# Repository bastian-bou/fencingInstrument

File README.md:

[![CC BY-NC-SA 4.0][cc-by-nc-sa-shield]][cc-by-nc-sa]

This work is licensed under a
[Creative Commons Attribution-NonCommercial-ShareAlike 4.0 International License][cc-by-nc-sa].

[![CC BY-NC-SA 4.0][cc-by-nc-sa-image]][cc-by-nc-sa]

[cc-by-nc-sa]: http://creativecommons.org/licenses/by-nc-sa/4.0/
[cc-by-nc-sa-image]: https://licensebuttons.net/l/by-nc-sa/4.0/88x31.png
[cc-by-nc-sa-shield]: https://img.shields.io/badge/License-CC%20BY--NC--SA%204.0-lightgrey.svg

# Antiphona

This is an art project name Antiphona from the artist [Alexandra Riss](https://alexandra-riss.fr/).

It transforms the movements of a fencer during a fight into musical notes.
The fight becomes a unique music.

The device consists of two tripods on either side of the fencing piste.
Each tripod consists of 3 IR sensors spaced 50cm apart and an electronic interface PCB between an arduino micro and the 3 sensors.

## Hardware

IR Sensors are tfmini-s [datasheet](pj2-sj-pm-tfmini-s-a00-product-mannual-en-2155.pdf)

They need 5V DC power supply but the communication is through a LVTTL (3.3V) UART interface.

As the result, the PCB include a level shifter from 3.3V to 5V for the arduino and because the arduino will interrogate each sensor one after the other, there is a 3-way analog multiplexer for each communication channel (RX, TX).  
The PCB also include decoupling capacitors, as all components including sensors are powered by the 5V from the USB port on the arduino.

## Software

To communicate with sensors, I made my own library according to the datasheet with only the functionalities I needed and my specificities, which were:
- multipexer management,
- retrieval of values from the 3 lidars,
- selection of the right value on the 3 sensors

Every 20ms we interrogate the sensors, and play a MIDI note on the USB interface only if a new valid distance is received.  
The MIDI note is played as a function of distance and relative speed. Each meter on the track corresponds to a note from C3 to B4, and the speed (as a function of the distance separating the old value from the new one) corresponds to the velocity of the note.

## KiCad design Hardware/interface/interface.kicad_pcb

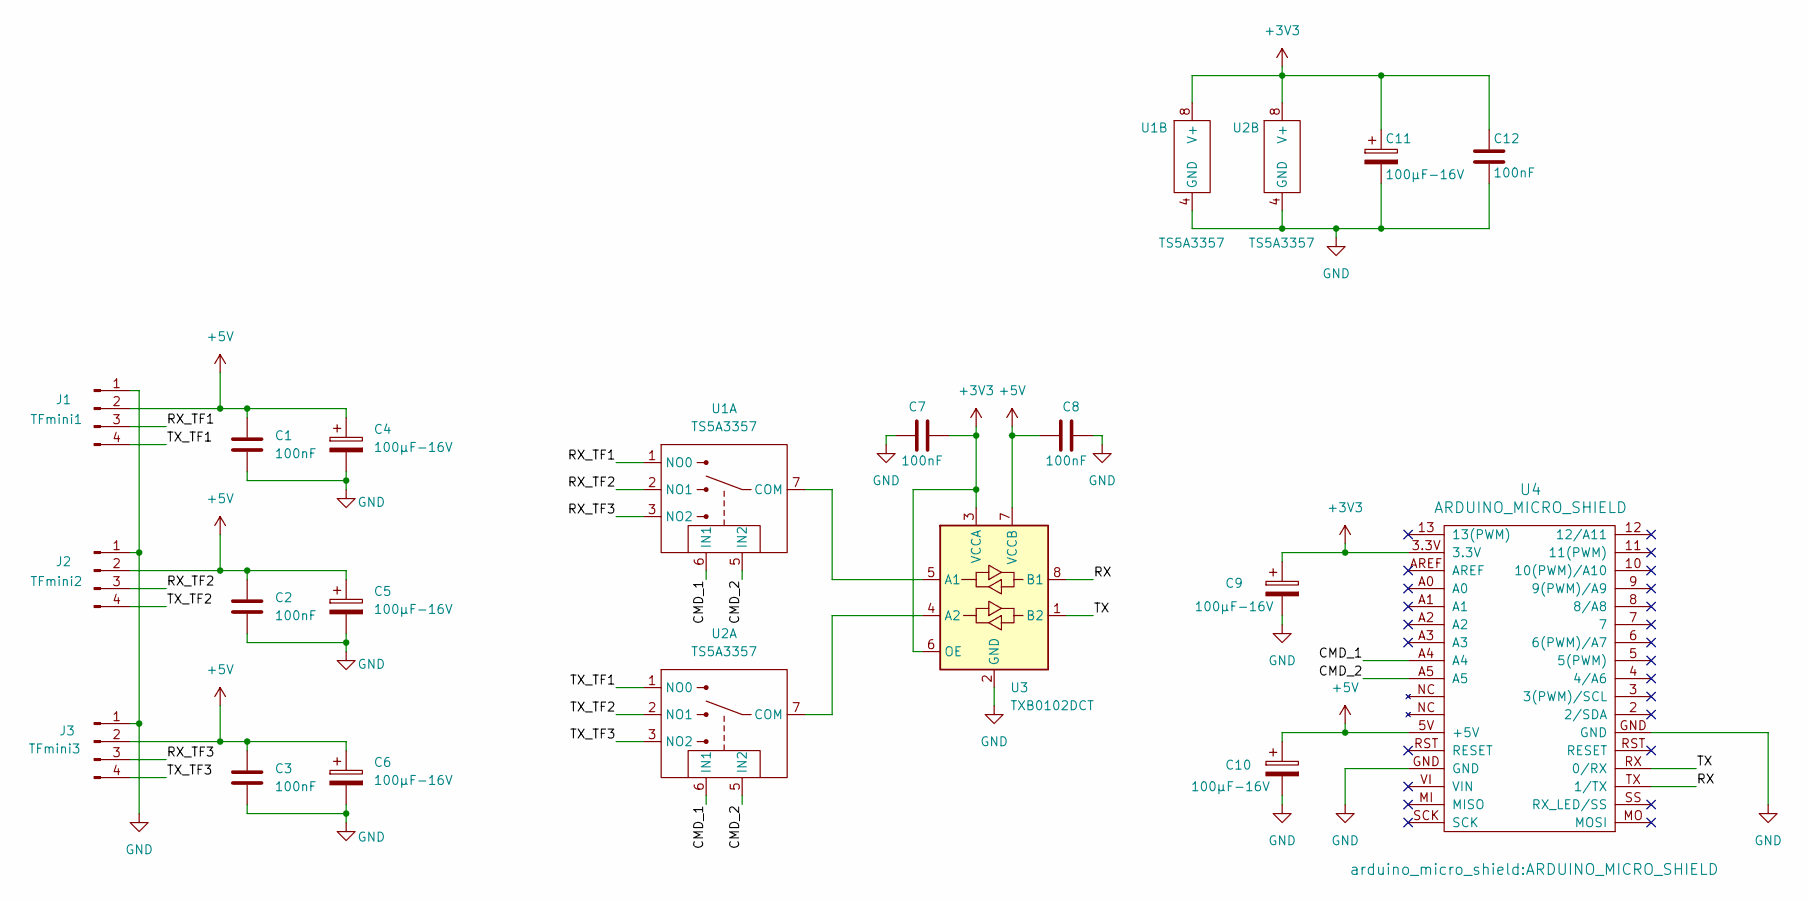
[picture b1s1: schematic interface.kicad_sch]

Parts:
C1, C2, C3, C7, C8, C12: 100nF; C_1206_3216Metric_Pad1.33x1.80mm_HandSolder
C4, C5, C6, C9, C10, C11: 100µF-16V; CP_Elec_6.3x5.7
J1: TFmini1; SolderWire-0.1sqmm_1x04_P3.6mm_D0.4mm_OD1mm_Relief
J2: TFmini2; SolderWire-0.1sqmm_1x04_P3.6mm_D0.4mm_OD1mm_Relief
J3: TFmini3; SolderWire-0.1sqmm_1x04_P3.6mm_D0.4mm_OD1mm_Relief
U1, U2: TS5A3357; VSSOP-8_3.0x3.0mm_P0.65mm
U3: TXB0102DCT; TSSOP-8_3x3mm_P0.65mm
U4: ARDUINO_MICRO_SHIELD

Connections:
+3V3: C7.1, C9.1, C11.1, C12.1, U1.8 (V+), U2.8 (V+), U3.3 (VCCA), U3.6 (OE), U4.3.3V
+5V: C1.1, C2.1, C3.1, C4.1, C5.1, C6.1, C8.1, C10.1, J1.2, J2.2, J3.2, U3.7 (VCCB), U4.5V (+5V)
/CMD_1: U1.6 (IN1), U2.6 (IN1), U4.A4
/CMD_2: U1.5 (IN2), U2.5 (IN2), U4.A5
/RX: U3.8 (B1), U4.TX (1/TX)
/RX_TF1: J1.3, U1.1 (NO0)
/RX_TF2: J2.3, U1.2 (NO1)
/RX_TF3: J3.3, U1.3 (NO2)
/TX: U3.1 (B2), U4.RX (0/RX)
/TX_TF1: J1.4, U2.1 (NO0)
/TX_TF2: J2.4, U2.2 (NO1)
/TX_TF3: J3.4, U2.3 (NO2)
GND: C1.2, C2.2, C3.2, C4.2, C5.2, C6.2, C7.2, C8.2, C9.2, C10.2, C11.2, C12.2, J1.1, J2.1, J3.1, U1.4 (GND), U2.4 (GND), U3.2 (GND), U4.GND
unnamed: U1.7 (COM), U3.5 (A1)
unnamed: U2.7 (COM), U3.4 (A2)

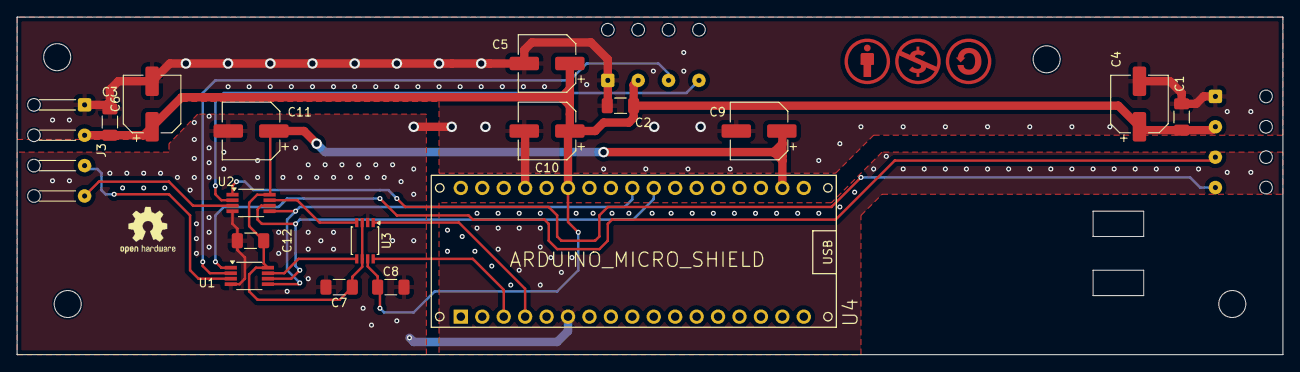
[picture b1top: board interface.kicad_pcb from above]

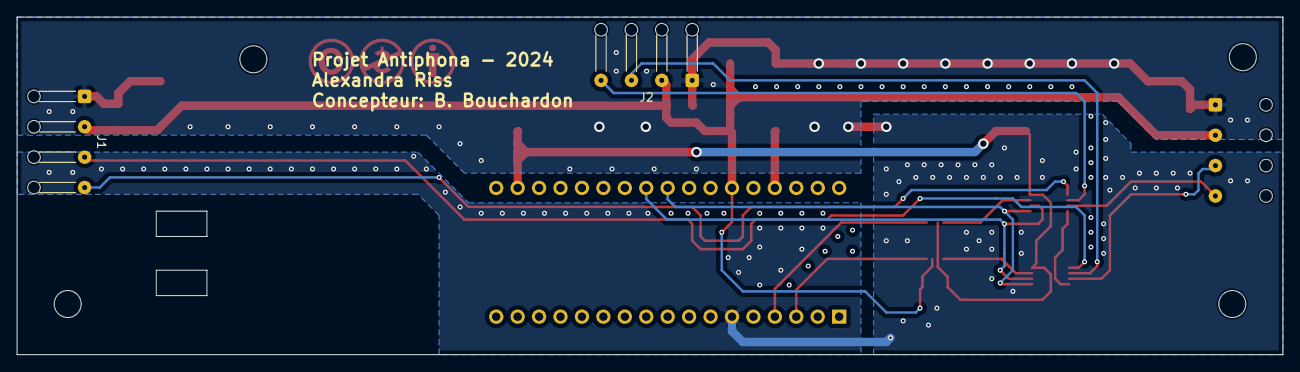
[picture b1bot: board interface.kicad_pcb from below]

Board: 2 copper layers, 150.0 x 40.0 mm, 19 parts (2 on the bottom side), 15 nets.

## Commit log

2022-08-31 add libs, testing complet on lidar, starting implementation of MIDI
2022-08-31 add extensions recommandation for vscode
2022-08-31 add debug, add different boards, add midi note, debug is running
2022-09-21 Change Licence, add midi, micro rules to compile, everything ...
2022-09-22 add max difference between two values
2024-04-20 add all current work on embedded code and add PCB interface for 3 lidars
2024-04-20 Almost finish PCB routing
2024-04-21 PCB finished and update gitignore with kicad files
2024-04-24 Add html bom
2024-05-09 Remove TF-mini library, tested with 3 lidar
2025-04-30 Add stuff in README Commit new changes on software from Victor Hugo on may 2024 Add tfminis datasheet
2025-06-22 Change sensor connectors to be more strong, efficient
